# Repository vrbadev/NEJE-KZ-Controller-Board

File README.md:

# NEJE-KZ Controller Board
Reverse-engineered schematic and layout for NEJE-KZ laser engraver controller board.

The schematic should be the same as for the original board. Parts should be correctly identified and connected. My goal was to find out the wiring to be able to replace the damaged original board with a board with my own design.

**Warning:** The reconstructed layout has not been manufactured or tested. Weird things can be found on this allegedly $25-worth Chinese board.

## BOM
| Qty | Part               | Value          | Package      | Additional info                |
|-----|--------------------|----------------|--------------|--------------------------------|
| 1   | C1                 | 560u/6.3V      | E2,5-7       |                                |
| 1   | C10                | 1n             | 0402         |                                |
| 4   | C2, C4, C5, C8     | 100n           | 0402         |                                |
| 1   | C3                 | 2n7            | 0402         |                                |
| 2   | C6, C7             | 1u             | 0603         |                                |
| 2   | C9, C11            | 1u             | 0805         |                                |
| 1   | D1                 | SS14           | SMA          | Schottky diode, 40V, 1A        |
| 1   | IC1                | STC8A4K16S2A12 | LQFP44-10X10 | STC8F family MCU               |
| 1   | IC2                | XC6206P332MR   | SOT23-3      | LDO, 3.3V, 200mA               |
| 1   | IC3                | AMS1117-5.0    | SOT223       | LDO, 5.0V, 1A                  |
| 1   | IC4                | CH340C         | SO16         | USB to Serial                  |
| 1   | IC5                | TX4223         | SOIC8        | DC-DC boost 5A converter       |
| 4   | IC6, IC7, IC8, IC9 | TC118S         | SOIC8        | Single channel DC motor driver |
| 1   | J1                 | USB-B          | USB-B-PTH    | USB B THT connector            |
| 1   | J10                | LASER-ST       | JST-XH-02    |                                |
| 1   | J11                | LASER_PLUS     | 1X04_1MM_RA  |                                |
| 1   | J12                | UART           | MA04-1       |                                |
| 1   | J2                 | DC 5.5/2.1mm   |              | THT DC jack connector          |
| 2   | J3, J4             | EX             | JST-XH-02    |                                |
| 1   | J5                 | LED-SW         | JST-XH-04    |                                |
| 1   | J6                 | MOTOR-X        | JST-XH-04    |                                |
| 1   | J7                 | MOTOR-Y        | JST-XH-04    |                                |
| 1   | J8                 | FAN            | JST-XH-02    |                                |
| 1   | J9                 | LASER-PWR      | JST-XH-02    |                                |
| 1   | L1                 | 470UH          | 8x8mm        | Eg. WE 74477724                |
| 1   | LED1               |                | 0805         |                                |
| 1   | Q1                 | SI2301         | SOT23-3      | P-Channel MOSFET               |
| 2   | Q2, Q3             | GMS2302AL      | SOT23-3      | N-Channel MOSFET               |
| 1   | R1                 | 1k             | 0402         |                                |
| 5   | R2, R3, R7, R8, R9 | 3k3            | 0402         |                                |
| 2   | R4, R10            | 10k            | 0402         |                                |
| 1   | R5                 | 270R           | 0402         |                                |
| 1   | R6                 | 6k2            | 0402         |                                |
| 1   | S1                 | BTN            | DTSM-3       | SMT Push-button                |

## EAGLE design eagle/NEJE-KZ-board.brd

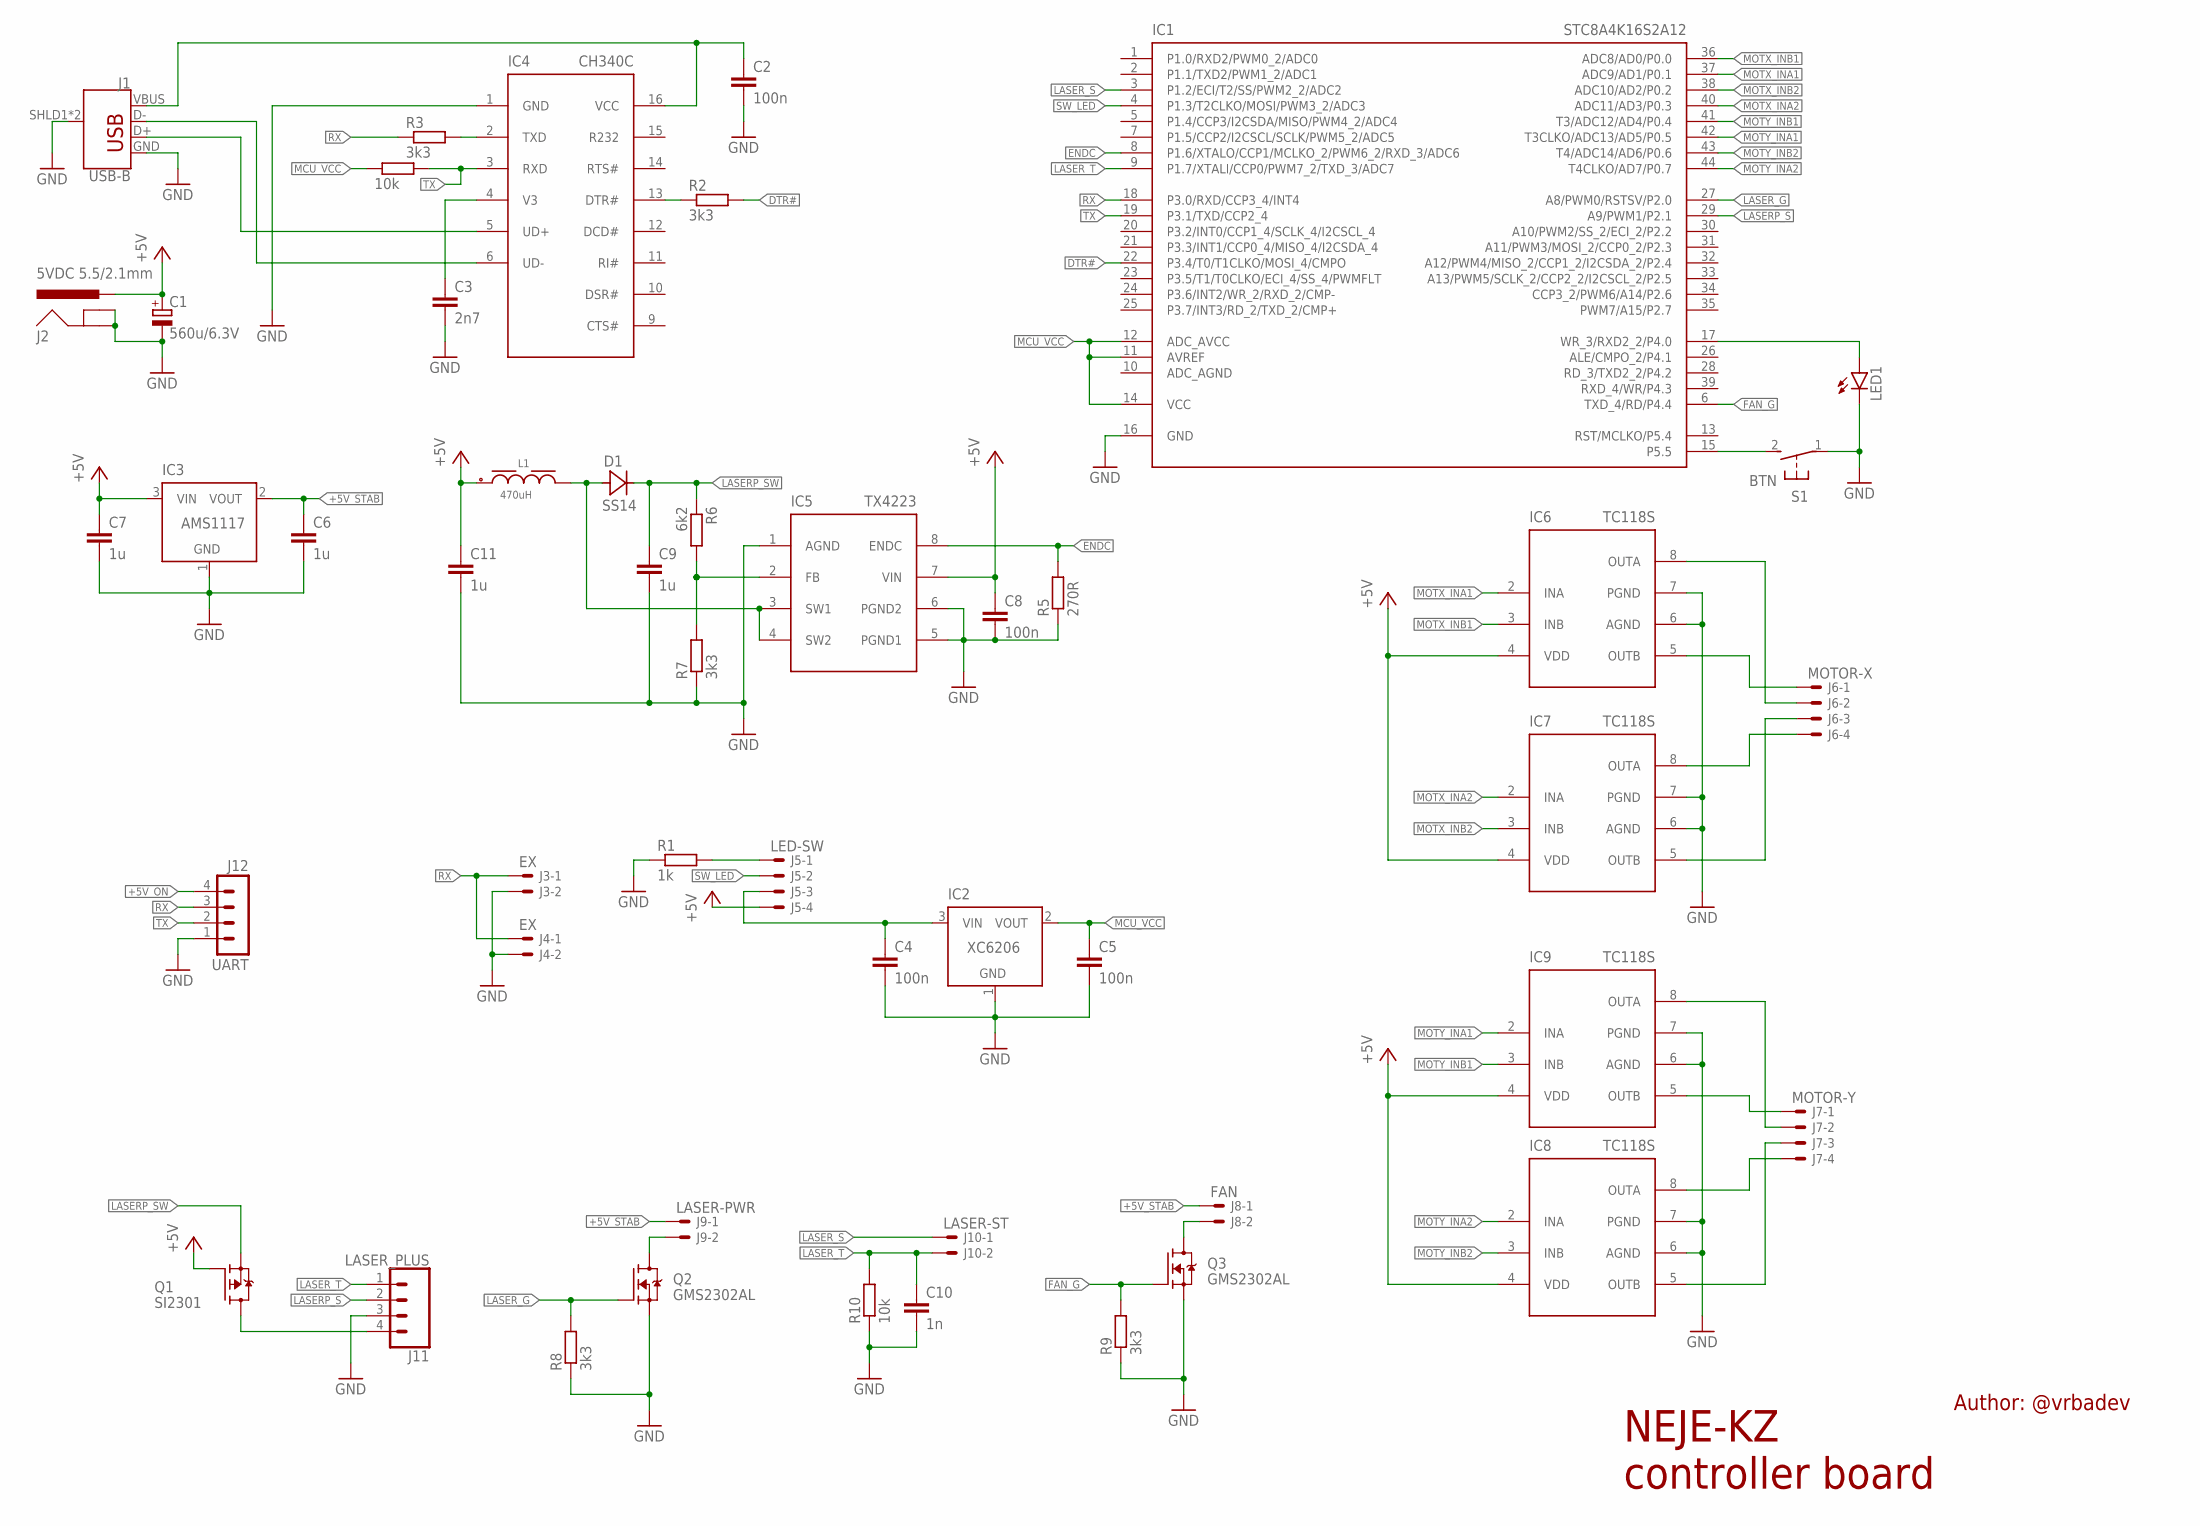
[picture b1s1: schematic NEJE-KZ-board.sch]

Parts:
C1: 560u/6.3V; E2,5-7
C2, C4, C5, C8: 100n; C0402
C3: 2n7; C0402
C6, C7: 1u; C0603
C9, C11: 1u; C0805
C10: 1n; C0402
D1: SS14; SMA
IC1: STC8A4K16S2A12; LQFP44-10X10
IC2: XC6206; SOT23-3
IC3: AMS1117; SOT223
IC4: CH340C; SO16
IC5: TX4223; SOIC8
IC6, IC7, IC8, IC9: TC118S; SOIC8
J1: USB-B; USB-B-PTH
J2: 5VDC 5.5/2.1mm; POWER_JACK_SLOT
J3, J4: EX; JST-XH-02-PACKAGE-LONG-PAD
J5: LED-SW; JST-XH-04-PACKAGE-LONG-PAD
J6: MOTOR-X; JST-XH-04-PACKAGE-LONG-PAD
J7: MOTOR-Y; JST-XH-04-PACKAGE-LONG-PAD
J8: FAN; JST-XH-02-PACKAGE-LONG-PAD
J9: LASER-PWR; JST-XH-02-PACKAGE-LONG-PAD
J10: LASER-ST; JST-XH-02-PACKAGE-LONG-PAD
J11: LASER_PLUS; 1X04_1MM_RA
J12: UART; MA04-1
L1: 470uH; WE-PD_7345
LED1: LEDCHIP-LED0805; CHIP-LED0805
Q1: SI2301; SOT23-3
Q2, Q3: GMS2302AL; SOT23-3
R1: 1k; R0402
R2, R3, R7, R8, R9: 3k3; R0402
R4, R10: 10k; R0402
R5: 270R; R0402
R6: 6k2; R0402
S1: BTN; DTSM-3

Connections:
+5V: C1.+, C7.1, C8.1, C11.1, IC3.3 (VIN), IC5.7 (VIN), IC6.4 (VDD), IC7.4 (VDD), IC8.4 (VDD), IC9.4 (VDD), J2.PWR, J5.4, L1.1, Q1.1 (G)
+5VUSB: C2.1, IC4.16 (VCC), J1.VBUS
+5V_ON: C4.1, IC2.3 (VIN), J5.3, J12.4
+5V_STAB: C6.1, IC3.2 (VOUT), J8.1, J9.1
BTN: IC1.15 (P5.5), S1.2
DTR#: IC1.22 (P3.4/T0/T1CLKO/MOSI_4/CMPO), R2.2
ENDC: IC1.8 (P1.6/XTALO/CCP1/MCLKO_2/PWM6_2/RXD_3/AD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), IC5.8 (ENDC), R5.2
FAN_G: IC1.6 (TXD_4/RD/P4.4), Q3.1 (G), R9.2
GND: C1.-, C2.2, C3.2, C4.2, C5.2, C6.2, C7.2, C8.2, C9.2, C10.2, C11.2, IC1.16 (GND), IC2.1 (GND), IC3.1 (GND), IC4.1 (GND), IC5.1 (AGND), IC5.5 (PGND1), IC5.6 (PGND2), IC6.6 (AGND), IC6.7 (PGND), IC7.6 (AGND), IC7.7 (PGND), IC8.6 (AGND), IC8.7 (PGND), IC9.6 (AGND), IC9.7 (PGND), J1.GND, J1.SHLD1 (SHIELD), J1.SHLD2 (SHIELD), J2.GND@1 (GNDBREAK), J2.GND@2 (GND), J3.2, J4.2, J11.3, J12.1, LED1.C, Q2.2 (S), Q3.2 (S), R1.1, R5.1, R7.1, R8.1, R9.1, R10.1, S1.1
LASERP_S: IC1.29 (A9/PWM1/P2.1), J11.2
LASERP_SW: C9.1, D1.C, Q1.2 (S), R6.1
LASER_G: IC1.27 (A8/PWM0/RSTSV/P2.0), Q2.1 (G), R8.2
LASER_S: IC1.3 (P1.2/ECI/T2/SS/PWM2_2/ADC2), J10.1
LASER_T: C10.1, IC1.9 (P1.7/XTALI/CCP0/PWM7_2/TXD_3/ADC7), J10.2, J11.1, R10.2
LED1: IC1.17 (WR_3/RXD2_2/P4.0), LED1.A
MCU_VCC: C5.1, IC1.11 (AVREF), IC1.12 (ADC_AVCC), IC1.14 (VCC), IC2.2 (VOUT), R4.1
MOTX_INA1: IC1.37 (ADC9/AD1/P0.1), IC6.2 (INA)
MOTX_INA2: IC1.40 (ADC11/AD3/P0.3), IC7.2 (INA)
MOTX_INB1: IC1.36 (ADC8/AD0/P0.0), IC6.3 (INB)
MOTX_INB2: IC1.38 (ADC10/AD2/P0.2), IC7.3 (INB)
MOTY_INA1: IC1.42 (T3CLKO/ADC13/AD5/P0.5), IC9.2 (INA)
MOTY_INA2: IC1.44 (T4CLKO/AD7/P0.7), IC8.2 (INA)
MOTY_INB1: IC1.41 (T3/ADC12/AD4/P0.4), IC9.3 (INB)
MOTY_INB2: IC1.43 (T4/ADC14/AD6/P0.6), IC8.3 (INB)
unnamed: C3.1, IC4.4 (V3)
unnamed: IC4.13 (DTR#), R2.1
unnamed: IC4.2 (TXD), R3.2
unnamed: J5.1, R1.2
unnamed: IC6.5 (OUTB), J6.1
unnamed: IC6.8 (OUTA), J6.2
unnamed: IC7.5 (OUTB), J6.3
unnamed: IC7.8 (OUTA), J6.4
unnamed: IC9.5 (OUTB), J7.1
unnamed: IC9.8 (OUTA), J7.2
unnamed: IC8.5 (OUTB), J7.3
unnamed: IC8.8 (OUTA), J7.4
unnamed: IC5.2 (FB), R6.2, R7.2
unnamed: J9.2, Q2.3 (D)
unnamed: J8.2, Q3.3 (D)
unnamed: J11.4, Q1.3 (D)
unnamed: D1.A, IC5.3 (SW1), IC5.4 (SW2), L1.2
RX: IC1.18 (P3.0/RXD/CCP3_4/INT4), J3.1, J4.1, J12.3, R3.1
SW_LED: IC1.4 (P1.3/T2CLKO/MOSI/PWM3_2/ADC3), J5.2
TX: IC1.19 (P3.1/TXD/CCP2_4), IC4.3 (RXD), J12.2, R4.2
USB_D+: IC4.5 (UD+), J1.D+
USB_D-: IC4.6 (UD-), J1.D-

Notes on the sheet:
NEJE-KZ controller board
Author: @vrbadev

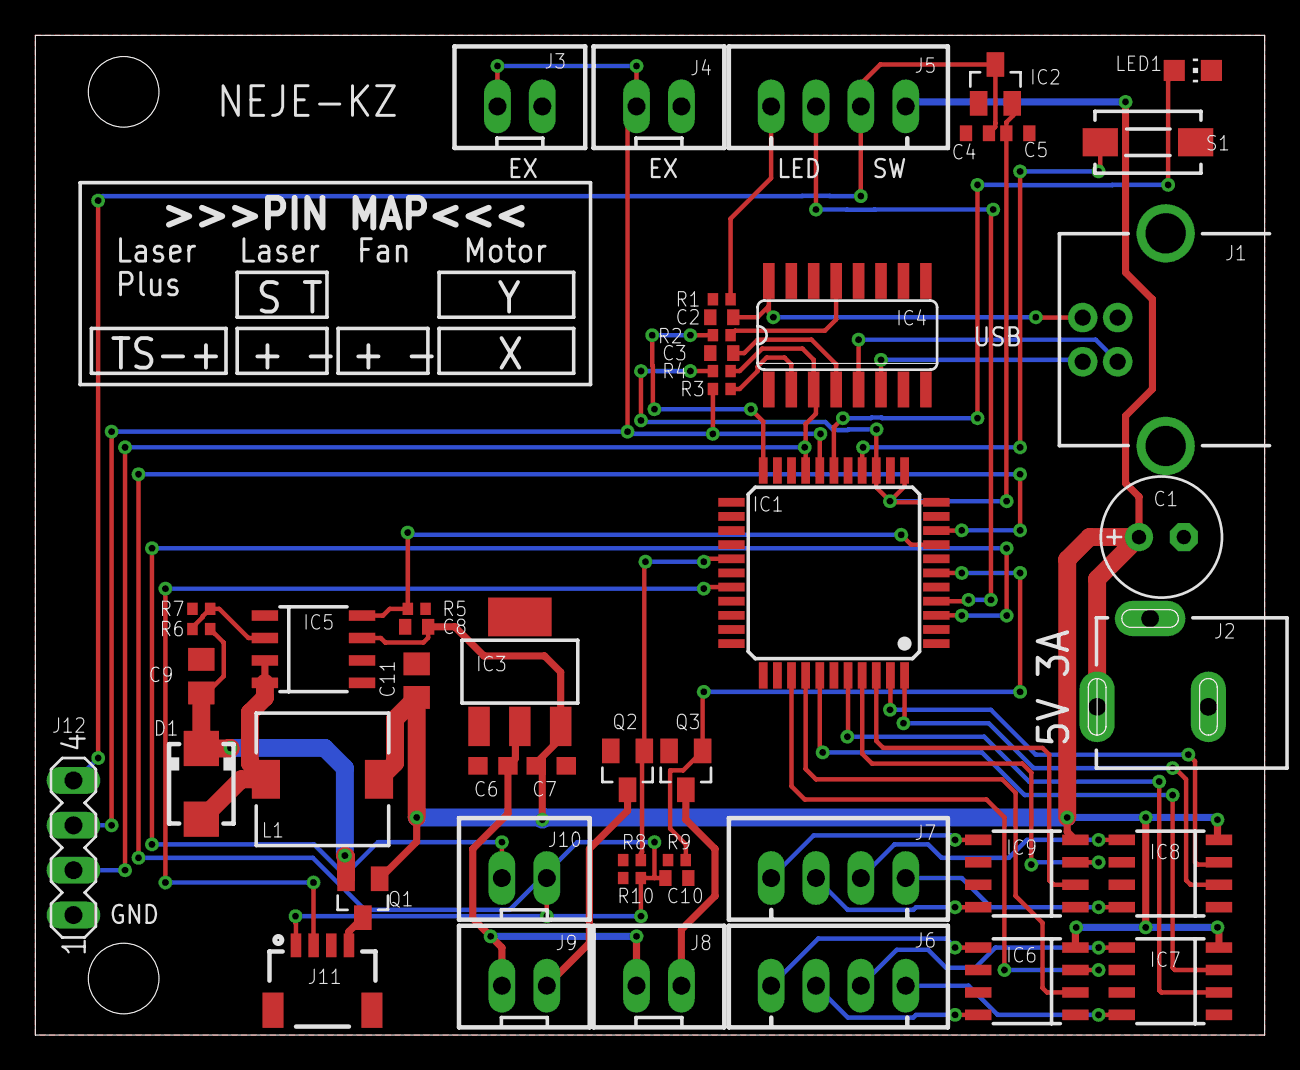
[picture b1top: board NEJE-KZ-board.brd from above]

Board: 2 copper layers, 69.6 x 56.6 mm, 49 parts (0 on the bottom side), 46 nets.

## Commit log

2020-11-19 Exported PDF
2020-11-19 Datasheet files
2020-11-19 Eagle files
2020-11-19 Photos and scans

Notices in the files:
parts and their libraries:
SparkFun-Connectors: Licensing: Creative Commons ShareAlike 4.0 International - https://creativecommons.org/licenses/by-sa/4.0
Eagle_WE-PD: Copyright: Würth Elektronik
